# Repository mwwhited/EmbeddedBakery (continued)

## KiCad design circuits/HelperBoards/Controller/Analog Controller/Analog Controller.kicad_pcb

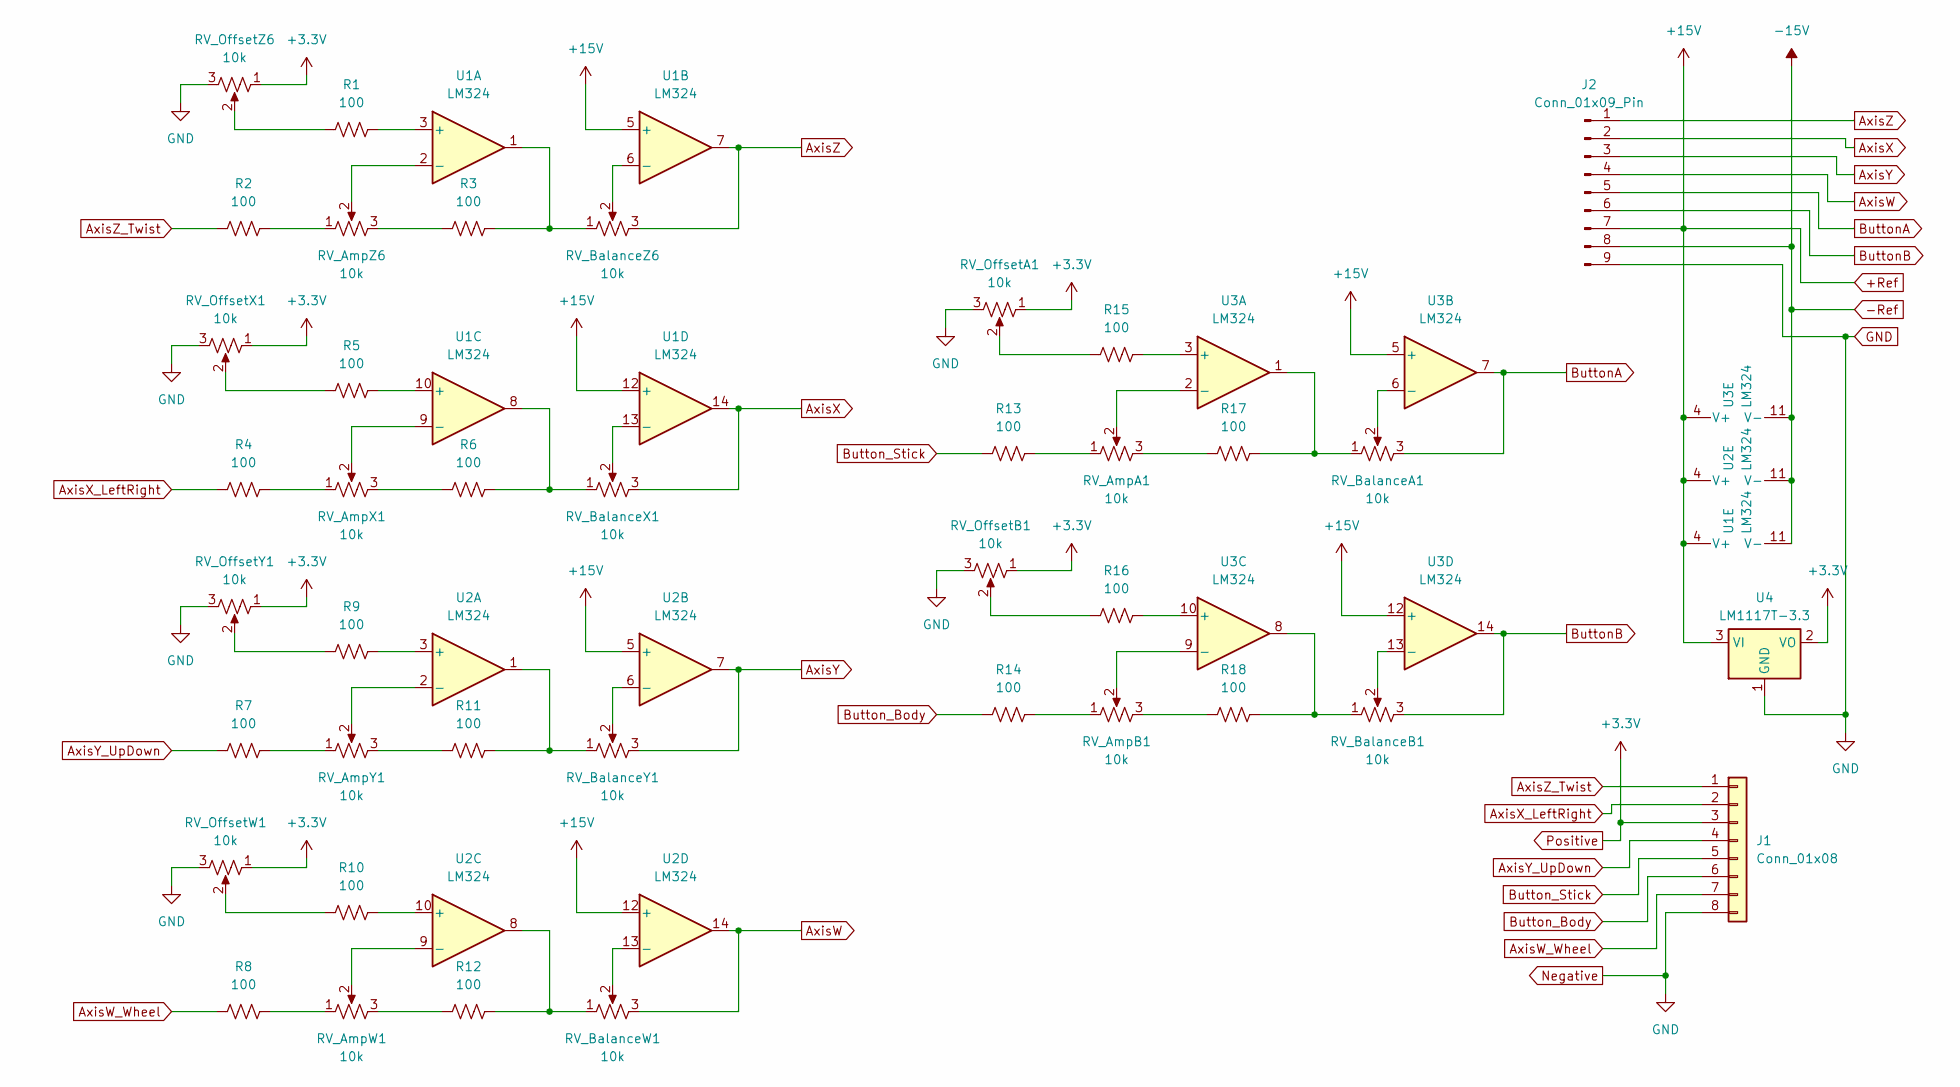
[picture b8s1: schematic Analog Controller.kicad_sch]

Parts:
J1: Conn_01x08; PinHeader_1x08_P1.00mm_Vertical
J2: Conn_01x09_Pin; PinHeader_1x09_P1.00mm_Vertical
R1, R2, R3, R4, R5, R6, R7, R8, R9, R10, R11, R12, R13, R14, R15, R16, R17, R18: 100; R_Axial_DIN0207_L6.3mm_D2.5mm_P10.16mm_Horizontal
RV_AmpA1: 10k; JST_XH_B3B-XH-AM_1x03_P2.50mm_Vertical
RV_AmpB1: 10k; JST_XH_B3B-XH-AM_1x03_P2.50mm_Vertical
RV_AmpW1: 10k; JST_XH_B3B-XH-AM_1x03_P2.50mm_Vertical
RV_AmpX1: 10k; JST_XH_B3B-XH-AM_1x03_P2.50mm_Vertical
RV_AmpY1: 10k; JST_XH_B3B-XH-AM_1x03_P2.50mm_Vertical
RV_AmpZ6: 10k; JST_XH_B3B-XH-AM_1x03_P2.50mm_Vertical
RV_BalanceA1: 10k; JST_XH_B3B-XH-AM_1x03_P2.50mm_Vertical
RV_BalanceB1: 10k; JST_XH_B3B-XH-AM_1x03_P2.50mm_Vertical
RV_BalanceW1: 10k; JST_XH_B3B-XH-AM_1x03_P2.50mm_Vertical
RV_BalanceX1: 10k; JST_XH_B3B-XH-AM_1x03_P2.50mm_Vertical
RV_BalanceY1: 10k; JST_XH_B3B-XH-AM_1x03_P2.50mm_Vertical
RV_BalanceZ6: 10k; JST_XH_B3B-XH-AM_1x03_P2.50mm_Vertical
RV_OffsetA1: 10k; JST_XH_B3B-XH-AM_1x03_P2.50mm_Vertical
RV_OffsetB1: 10k; JST_XH_B3B-XH-AM_1x03_P2.50mm_Vertical
RV_OffsetW1: 10k; JST_XH_B3B-XH-AM_1x03_P2.50mm_Vertical
RV_OffsetX1: 10k; JST_XH_B3B-XH-AM_1x03_P2.50mm_Vertical
RV_OffsetY1: 10k; JST_XH_B3B-XH-AM_1x03_P2.50mm_Vertical
RV_OffsetZ6: 10k; JST_XH_B3B-XH-AM_1x03_P2.50mm_Vertical
U1, U2, U3: LM324; DIP-14_W7.62mm_Socket
U4: LM1117T-3.3; TO-220-3_Horizontal_TabDown

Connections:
+Ref: J2.7, U1.4 (V+), U1.5 (+), U1.12 (+), U2.4 (V+), U2.5 (+), U2.12 (+), U3.4 (V+), U3.5 (+), U3.12 (+), U4.3 (VI)
-Ref: J2.8, U1.11 (V-), U2.11 (V-), U3.11 (V-)
AxisW: J2.4, RV_BalanceW1.3, U2.14
AxisW_Wheel: J1.7, R8.1
AxisX: J2.2, RV_BalanceX1.3, U1.14
AxisX_LeftRight: J1.2, R4.1
AxisY: J2.3, RV_BalanceY1.3, U2.7
AxisY_UpDown: J1.4, R7.1
AxisZ: J2.1, RV_BalanceZ6.3, U1.7
AxisZ_Twist: J1.1, R2.1
ButtonA: J2.5, RV_BalanceA1.3, U3.7
ButtonB: J2.6, RV_BalanceB1.3, U3.14
Button_Body: J1.6, R14.1
Button_Stick: J1.5, R13.1
GND: J1.8, J2.9, RV_OffsetA1.3, RV_OffsetB1.3, RV_OffsetW1.3, RV_OffsetX1.3, RV_OffsetY1.3, RV_OffsetZ6.3, U4.1 (GND)
unnamed: R1.1, RV_OffsetZ6.2
unnamed: R2.2, RV_AmpZ6.1
unnamed: R3.1, RV_AmpZ6.3
unnamed: R3.2, RV_BalanceZ6.1, U1.1
unnamed: R4.2, RV_AmpX1.1
unnamed: R5.1, RV_OffsetX1.2
unnamed: R6.1, RV_AmpX1.3
unnamed: R6.2, RV_BalanceX1.1, U1.8
unnamed: R7.2, RV_AmpY1.1
unnamed: R8.2, RV_AmpW1.1
unnamed: R9.1, RV_OffsetY1.2
unnamed: R10.1, RV_OffsetW1.2
unnamed: R11.1, RV_AmpY1.3
unnamed: R11.2, RV_BalanceY1.1, U2.1
unnamed: R12.1, RV_AmpW1.3
unnamed: R12.2, RV_BalanceW1.1, U2.8
unnamed: R13.2, RV_AmpA1.1
unnamed: R14.2, RV_AmpB1.1
unnamed: R15.1, RV_OffsetA1.2
unnamed: R16.1, RV_OffsetB1.2
unnamed: R17.1, RV_AmpA1.3
unnamed: R17.2, RV_BalanceA1.1, U3.1
unnamed: R18.1, RV_AmpB1.3
unnamed: R18.2, RV_BalanceB1.1, U3.8
unnamed: R1.2, U1.3 (+)
unnamed: RV_AmpZ6.2, U1.2 (-)
unnamed: RV_BalanceZ6.2, U1.6 (-)
unnamed: R5.2, U1.10 (+)
unnamed: RV_AmpX1.2, U1.9 (-)
unnamed: RV_BalanceX1.2, U1.13 (-)
unnamed: R9.2, U2.3 (+)
unnamed: RV_AmpY1.2, U2.2 (-)
unnamed: RV_BalanceY1.2, U2.6 (-)
unnamed: R10.2, U2.10 (+)
unnamed: RV_AmpW1.2, U2.9 (-)
unnamed: RV_BalanceW1.2, U2.13 (-)
unnamed: R15.2, U3.3 (+)
unnamed: RV_AmpA1.2, U3.2 (-)
unnamed: RV_BalanceA1.2, U3.6 (-)
unnamed: R16.2, U3.10 (+)
unnamed: RV_AmpB1.2, U3.9 (-)
unnamed: RV_BalanceB1.2, U3.13 (-)
Positive: J1.3, RV_OffsetA1.1, RV_OffsetB1.1, RV_OffsetW1.1, RV_OffsetX1.1, RV_OffsetY1.1, RV_OffsetZ6.1, U4.2 (VO)

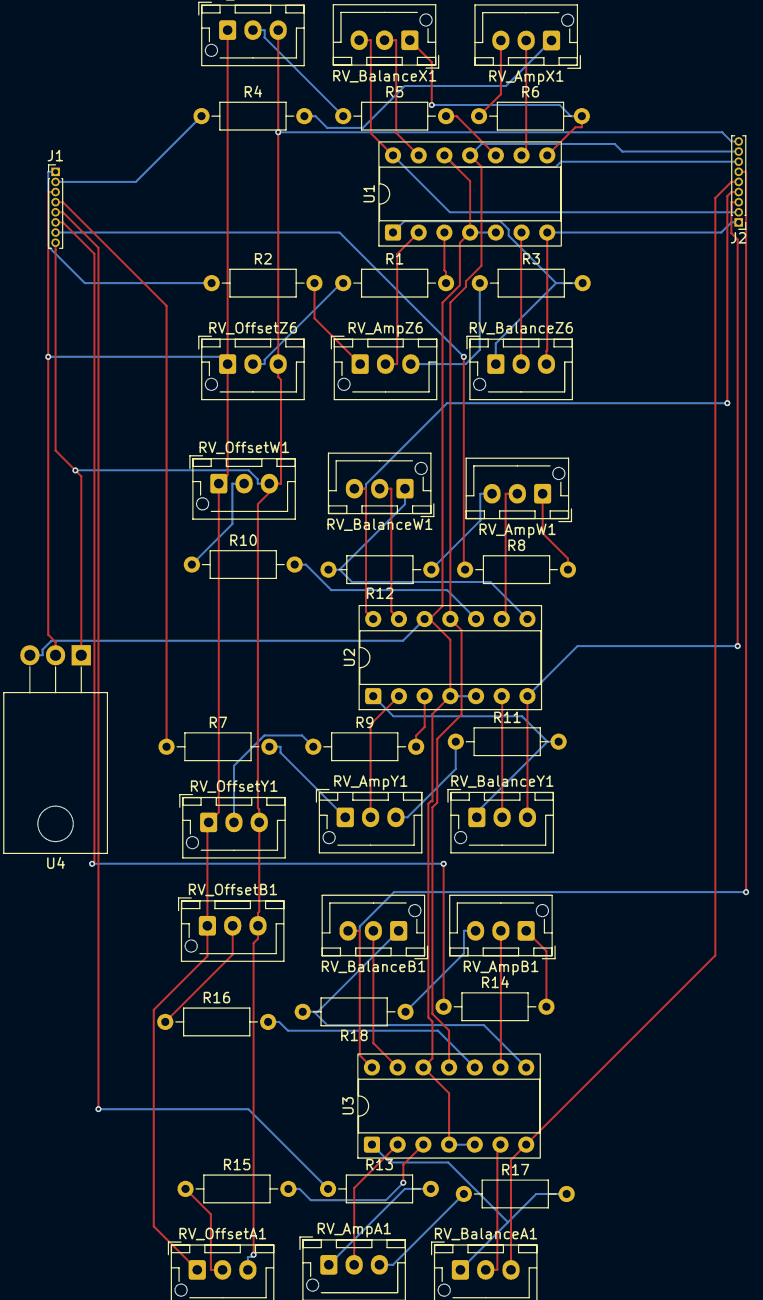
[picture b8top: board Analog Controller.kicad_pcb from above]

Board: 2 copper layers, 42 parts (0 on the bottom side), 58 nets.

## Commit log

2020-11-25 first push
2020-11-26 Found more good stuff
2020-12-02 update diagrams and import some other code
2020-12-02 Update kicad layouts
2020-12-16 Update diagrams for fencing machine interfaces
2021-01-15 arty test code
2021-01-16 clean up
2021-01-30 udpate model
2021-01-31 Create ARTY A7 Test Project
2021-02-01 update designs
2021-02-18 Add arty test projects
2021-02-18 Update arty 100 default constraints file
2021-02-18 converted demo for pmodenc to support Arty
2021-02-19 start a rom editor
2021-02-21 working on similar calculator
2021-02-21 clock divider is now working
2021-02-21 Got keypad working
2021-02-22 keypad working, started registers
2021-02-22 create nibble reader
2021-02-22 create nibble writer
2021-02-24 Create a test i2c module
2021-02-24 i2c write single byte
2021-02-24 changed i2c to use High-Z instead of being driven high.
2021-02-25 Start statemachine for i2c lcd
2021-02-25 test creating a custom IP for the IP Catalog
2021-02-25 Revert "test creating a custom IP for the IP Catalog"
    This reverts commit c07ab34091df91f1932734a7cfe39c503ffb506f.
2021-02-25 Add old arduino test projects
2021-02-25 Add old Xilinx xc9500 CPLD projects
2021-02-25 update quartus/ep2c5 projects
2021-02-25 Started RowColumnDecoder as shared IP
2021-03-01 Fixed Row Column Decoder to make synthesis possible
2021-03-01 update vivado package for rowcolumndecoder
2021-03-02 repackage row col decoder
2021-03-03 Create simple clock divider IP
2021-03-03 clean up simulation
2021-03-03 Fix row decoder
2021-03-03 update Ip Catalog for RowColumnDecoder
2021-03-03 update row column decoder
2021-03-03 change simple calc to use shared ip catalog
2021-03-04 cleanup and start my own VGA
2021-03-04 My VGA code works for a test pattern
2021-03-04 not quite right... but time for sleep
2021-03-04 vga test run ... its alive!
2021-03-04 cleaned up text mode.. made it a mod4 versus mod3... looks much cleaner.
2021-03-05 vga update
2021-03-05 Create IP for PMOD VGA Text Mode
2021-03-05 Create IP for PMOD VGA Text Mode 2
2021-03-05 create custom pmodkypd based on rowcolumndecoder
2021-03-05 try VGA as IP
2021-03-10 rollback VGA from Calc and IP
2021-03-10 axi mig ddr tutorial
2021-03-11 clean up ip and start emulator
2021-03-11 another try ad character rom
2021-03-12 create character rom unit
2021-03-12 color matrix
2021-03-12 color matrix combinational
2021-03-12 color palette combinational
2021-03-13 text rendering
2021-03-13 text mode
2021-03-13 add change detection to row column decoder
2021-03-13 add change detection to row column IP package
2021-03-13 update and cleanup child IP for PMod Keypad
2021-03-13 update and cleanup child IP for PMod Keypad again
2021-03-14 Add change detection to rew/column decoder
2021-03-14 update ip package to include change detection to rew/column decoder
2021-03-14 added change detection to pmod keypad ip
2021-03-14 start working on fifo
2021-03-14 progress
2021-03-15 still working on fifo/keyboard buffer
2021-03-16 update keypad
2021-03-16 make keypad work again
2021-03-17 fifo test
2021-03-18 fifo example
2021-03-18 fifo example... progress, at least reset works
2021-03-18 FIFO Example is working!
2021-03-18 Extend constaints file to support pmod shield
2021-03-20 IT WORKS! ... Keypad FIFO writing works!
2021-03-20 Triggered FIFO Writed IP Created
2021-03-21 FIFO to BRAM works
2021-03-22 Remove old files
2021-03-22 clean up IP
2021-03-22 Clean up Arty constraints
2021-03-22 working on text rendering with fifo/blockram
2021-03-29 fix up
2021-03-31 test custom pmod led 8x8
2021-03-31 test custom pmod 16bit switch banked
2021-03-31 copy in schematics for custom pmods
2021-03-31 remove remapping and add rotation
2021-04-03 fix up 16 bit banked key
2021-04-11 update pmod16bit
2022-12-09 update changes. at pic playground
2022-12-13 add other projects
2022-12-13 change back to 10 bit and fix variables
2023-01-01 update examples for ESP-01, ESP32, Particle Spark Core/Photon
2023-01-01 update notes
2023-01-02 stub out clock for attiny2313
2023-01-02 Bump System.Drawing.Common in /src/tools/BinaryBaker/RomFonts
    Bumps [System.Drawing.Common](https://github.com/dotnet/runtime) from 5.0.1 to 5.0.3.
    - [Release notes](https://github.com/dotnet/runtime/releases)
    - [Commits](https://github.com/dotnet/runtime/compare/v5.0.1...v5.0.3)
    ---
    updated-dependencies:
    - dependency-name: System.Drawing.Common
2023-01-02 Bump System.Drawing.Common in /src/tools/BinaryBaker/ImageBuilder
    Bumps [System.Drawing.Common](https://github.com/dotnet/runtime) from 5.0.1 to 5.0.3.
    - [Release notes](https://github.com/dotnet/runtime/releases)
    - [Commits](https://github.com/dotnet/runtime/compare/v5.0.1...v5.0.3)
    ---
    updated-dependencies:
    - dependency-name: System.Drawing.Common
2023-01-02 using internal oscillator and default multiplier
2023-01-02 update time
2023-01-03 clock working
2023-01-03 sketch up circuits
2023-01-07 update clock
2023-01-07 Fix schematics and coding
2023-01-07 update design
2023-01-07 update readme for simple clock
2023-02-21 add stuff
2023-02-22 Add scripts and update controller code
2023-03-08 build out circuits
2023-03-08 add circuits
2023-03-08 update circuits
2023-03-08 cleanup circuits
2023-03-08 Add helper boards
2023-03-09 update layount
2023-03-09 update analog computer layout
2023-03-19 migrate old code
2023-03-19 swap out SD.h for SDFat.h
2023-03-27 update and save PDF files
2023-03-30 update libraries, stub out example IO board pcb, start looking at freertos
2023-04-23 update libraries
2023-04-23 stub out stm32 example
2023-04-23 try arduino blen micro redbearlab
2023-04-23 add mapping
2023-04-24 Add ring buffer library and stub out RTOS example
2023-04-24 update script
2023-04-26 update keyboard
2023-04-27 update examples
2023-05-01 update keyboard mapping
2023-10-11 add examples
2025-01-15 first pass
2025-01-18 more toys
2025-01-18 pile of hacks
2025-01-24 update microcode builder
2025-01-24 Improve MicroCode def
2025-01-31 update table
2025-01-31 update micro code
2025-02-08 update frameworks
2025-02-14 Update LICENSE
2025-02-16 update references
2025-03-24 add analog converter
2025-05-01 add timer
2025-05-01 add the ability to disable logging
2025-05-02 change to support multiple devices
2025-05-02 update code
2025-05-02 update timer
2025-05-03 add debugging
2025-05-03 fix logging and support multiple boards with the same pinout
2025-05-03 update changes adding watchdog timer, input validation and time remaining
2025-05-03 this dont wont
2025-05-03 change pinout
2025-05-03 add show all settings
2025-08-01 Auto-commit:
2025-08-04 update arduino libs
2025-12-06 working
2025-12-06 migrate
2025-12-13 start notes
2025-12-13 review and describe projects
2025-12-26 update phase1 AI
2025-12-26 start line follower hack
2026-01-08 update all
2026-01-09 add 8051
2026-01-09 add .net micro framework projects
2026-01-09 migrated
2026-04-09 Add more designs
